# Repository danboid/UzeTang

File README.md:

# UzeTang

A [Uzebox](https://uzebox.org) console core for the **Sipeed Tang Nano 20K**
FPGA, based on the [Uzebox Omega](https://github.com/danboid/uzebox-omega) design.

- **CPU:** a new, cycle-exact ATmega644 core. It is verified in lock-step,
  cycle by cycle, against the
  [CUzeBox-ex](https://github.com/weber21w/cuzebox-ex) emulator.
- **Video and audio:** HDMI at 720×480p, 59.94 Hz, with 48 kHz audio. There is
  no composite output and no AD725.
- **Games:** loaded from the micro SD card by the standard Uzebox
  **Bootloader5** game loader, which ships in the bitstream.
- **Controllers:** two SNES pads on the same pins and adapters as
  [SNESTang](https://github.com/nand2mario/snestang/blob/main/doc/installation.md).
- **SPI RAM:** 8 MB, emulated in the board's built-in SDRAM (all of it)
  (23LC1024-compatible: READ, WRITE, RDMR and WRMR, with byte, page and
  sequential modes; 24-bit addresses). The kernel's `SpiRamInitGetSize()`
  reports 128 banks of 64 KB, as CUzeBox-ex does with 8 MB.

Not implemented yet: DualShock 2 adapters (their pins are kept free) and EEPROM saving
across power cycles. There are likely other missing features.

There is an experimental UzeTang PCB that fits within the Uzebox 3D printed case but
it has not been tested at all yet so try it at your own risk.

I don't plan to port it to any other Tang boards but I would like to see it ported
to the Spectrum Next, MEGA65 and other open source modern retro FPGA based computers.

See [this forum topic](https://uzebox.org/forums/viewtopic.php?t=11951) for discussion and more information about UzeTang.

## Hardware

| Function | Tang Nano 20K pins | Notes |
|---|---|---|
| HDMI | on-board connector | 720×480p, 4:3, HDMI with 48 kHz audio |
| micro SD | on-board slot | SPI mode, FAT16/FAT32, SD and SDHC |
| SNES pad 1 | latch 28, clock 27, data 25 | as SNESTang |
| SNES pad 2 | latch 29, clock 26, data 30 | as SNESTang |
| S1 button | 88 | reset (see below) |
| S2 button | 87 | hold for free-running video (no frame lock), for diagnosis |
| LED0 / LED1 | 15 / 16 | SD access / slow blink = video OK, fast blink = no video sync |

Pins 17–20 (SNESTang's DualShock 2 adapter) are left unused.

## Using it

1. Format a micro SD card as FAT32 (or FAT16) and copy `.uze` games onto it.
2. Flash the bitstream to the Tang Nano 20K (see [Flashing](#flashing)).
3. Power up. As on a real Uzebox, Bootloader5 first watches the controller for
   about ¾ s:
   - If the card holds exactly one `.uze`, it is flashed and started.
   - Otherwise the **game selector** opens.
   - At power-up the AVR's flash and EEPROM are blank, so you always start in
     the selector.
4. Choose a game with **Up/Down** and press **Start** (or Select). The game is
   written into the AVR's flash, which takes a second or two, and then starts.
5. **S1** resets the console. Hold any pad button while pressing S1 to return to
   the selector. **B** in the selector switches between "reset starts the game"
   and "reset opens the menu"; this setting is kept until power-off. In game,
   Start+Select+Y+B is the usual Uzebox soft reset.

## Flashing

UzeTang is flashed like any other Tang Nano 20K core, with openFPGALoader or
the Gowin programmer.

### Installing openFPGALoader on Debian and Ubuntu

openFPGALoader is in the standard Debian and Ubuntu repositories:

```
sudo apt update
sudo apt install openfpgaloader
```

Older releases ship an old version that does not know the Tang Nano 20K
(`openFPGALoader --list-boards | grep tangnano20k` prints nothing). In that
case build it from source, as described in the
[openFPGALoader install guide](https://trabucayre.github.io/openFPGALoader/guide/install.html)
and Sipeed's [Flashing on Linux](https://wiki.sipeed.com/hardware/en/tang/Tang-Nano-Doc/flash-in-linux.html)
page:

```
sudo apt install git gzip libftdi1-2 libftdi1-dev libhidapi-hidraw0 libhidapi-dev \
    libudev-dev zlib1g-dev cmake pkg-config make g++
git clone https://github.com/trabucayre/openFPGALoader.git
cd openFPGALoader && mkdir build && cd build
cmake .. && make -j$(nproc) && sudo make install
```

To use it without `sudo`, install the udev rules (see the install guide) and
add yourself to the `plugdev` group.

### Writing the bitstream

Connect the Tang Nano 20K by USB, then:

```
openFPGALoader -f uzetang.fs
```

`-f` writes to the board's flash, so UzeTang starts every time the board is
powered on. Add `-b tangnano20k` if openFPGALoader does not detect the board
on its own. Without `-f`, the bitstream is only loaded into the FPGA and is
lost at power-off, which is handy for a quick test.

Alternatively you can try flashing uzetang-oss.fs which is the same code
synthesized into a bitstream using an open source toolchain.

## Building

### Installing the Gowin IDE

Follow Sipeed's [Install the IDE](https://wiki.sipeed.com/hardware/en/tang/Tang-Nano-Doc/install-the-ide.html)
guide. In short:

- Download the **Education Edition** from Gowin's website. It needs no licence;
  the Standard Edition needs a licence file from Gowin.
- On Linux, unpack the archive. The tools are in its `IDE/bin` folder (`gw_ide`
  for the IDE, `gw_sh` for scripted builds such as UzeTang's).
- On Windows, run the installer with all components selected, then install the
  two drivers it offers.
- Sipeed suggests openFPGALoader (above) for flashing on Linux, as the Gowin
  programmer does not always work with the Tang boards' USB-JTAG.

### Gowin EDA

From the UzeTang folder (adjust the path to where you unpacked Gowin):

```
env -u DISPLAY -u WAYLAND_DISPLAY QT_QPA_PLATFORM=offscreen LIBGL_ALWAYS_SOFTWARE=1 \
    ~/Gowin_V1.9.11.03_Education_Linux/IDE/bin/gw_sh build.tcl
```

This produces `impl/pnr/uzetang.fs`. Use the Gowin Education Edition 1.9.9 or
newer, the same as SNESTang (tested with V1.9.11.03 on Debian 12). This build
uses Gowin's own I/O settings for the pad pins (pull-ups) and emulated LVDS
for HDMI, exactly as SNESTang does.

`gw_sh` has no window, but it still loads Qt and OpenGL. The `env` settings
above hide the desktop from it and ask for software rendering. Without them,
`gw_sh` can abort with "Could not load the Qt platform plugin "xcb"" and a
core dump, or with `libGL error` / `X Error ... GLX`. If it still fails,
install Mesa's OpenGL drivers (`sudo apt install libgl1-mesa-dri`), or run it
in a virtual X server (`sudo apt install xvfb`, then
`xvfb-run -a .../gw_sh build.tcl`).

The timing report (`impl/pnr/uzetang.tr.html`) lists setup and hold
violations for a clock called `sys/hdmi_out/aud_acc[0]`. They are false: that
is the 48 kHz audio clock, which is made from the pixel clock and only feeds
the HDMI audio sample handover. Gowin assumes it runs at 100 MHz with no
relationship to the pixel clock. Check `clk_cpu` (28.688 MHz needed) and
`clk_pix` (27 MHz needed) in the Max Frequency Summary instead.

### Open source (yosys + nextpnr-himbaechel + apicula)

```
NEXTPNR=nextpnr-himbaechel syn/oss_build.sh
```

This produces `syn/out/uzetang_oss.fs`. yosys cannot read hdl-util's
SystemVerilog HDMI encoder, so this flow uses `rtl/hdmi/hdmi_lite.v`, a plain
Verilog HDMI encoder written for UzeTang. It sends real HDMI with:

- data islands on every line (two packets each);
- an AVI InfoFrame (RGB, 4:3, full range, IT content / graphics);
- an Audio InfoFrame, Audio Clock Regeneration (N 6144, CTS 27000) and 48 kHz
  L-PCM audio sample packets;
- vsync edges aligned with the hsync leading edge, as CEA-861 requires, and at
  least 12 control characters before every preamble, as the HDMI compliance
  test requires.

apicula only allows true LVDS buffers on the HDMI pins, so this flow uses
`TLVDS_OBUF`. The Gowin flow uses emulated LVDS (`ELVDS_OBUF`), as SNESTang
does.

**SNES pads and I/O bank 5.** The SNES pad pins (25–30) share I/O bank 5 with
the HDMI pins. With true LVDS outputs in the bank, apicula's `gowin_pack`
(0.35) configures the whole bank for a low voltage, and it also sets two
configuration bits on the pad data inputs differently from the Gowin IDE: it
leaves `CLAMP=PCI` off and sets an input-standard bit that belongs to the
differential / reference-voltage standards. With that bitstream the pad data
line reads wrongly. Every pressed button also shows up as the next one in the
SNES bit order, B reads as held, and START reads as START+UP, so Bootloader5
loads the game above the highlighted one.

`syn/oss_build.sh` therefore packs through `tools/gowin_pack_bank33.py`, a
small wrapper around apicula's `gowin_pack`. It keeps banks with LVDS outputs
at the board's real 3.3 V and sets those pad-input bits as the Gowin IDE sets
them. The pad pins' I/O configuration then decodes identically to the Gowin
build's, and the pads work in both builds. To check that against a Gowin
bitstream, `tools/gowin_pack_bank33.py --iob-from uzetang.fs ...` copies the
pad tiles' I/O fuses from it instead.

The results below are from yosys 0.33 and nextpnr-himbaechel master
(Nov 2026), for the GW2AR-LV18QN88C8/I7:

| Resource | Used | Available |
|---|---|---|
| LUT4 (after packing, nextpnr) | 15,610 | 20,736 (75%) |
| Flip-flops | 2,544 | 15,552 (16%) |
| Block RAM | 41 | 46 (89%) |
| AVR clock Fmax | 31.7 MHz | needs 28.69 MHz |
| Pixel clock Fmax | 66 MHz | needs 27 MHz |

### Bootloader

The AVR flash's boot section (0xF000) holds Bootloader5 as the block RAM's
initial contents, generated from `firmware/bootloader5.hex`:

```
python3 tools/hex2mem.py --gowin-init firmware/bootloader5.hex rtl/bootloader_init.vh
```

## Verification

All test benches are in `sim/` (Verilator):

- **`tb_lockstep`** (`Vavr_soc`, or `Vls_top` with the SPI RAM emulation, the
  SDRAM controller and an SDRAM model) compiles the CUzeBox-ex AVR core in as a
  reference.
  - At every instruction it compares PC, cycle count, r0–r31, SREG and SP.
  - Every *N* instructions it also compares all of SRAM and the I/O registers.
  - `tests/run_fuzz.sh` generates random instruction streams, with Timer1,
    SPI and USART interrupts, PINx toggles, 16-bit timer writes and EEPROM
    strobes.
  - `tests/run_demos.sh` runs the Uzebox repository's games and demos, which
    are built with `tools/build_demo.py`.
- **`sim/hdmi`** checks the open-source HDMI encoder. `tb_hdmi.v` (Icarus
  Verilog) writes three frames of TMDS symbols, and `check_hdmi.py` decodes
  them the way a display does. It checks the period structure and guard
  bands, every video pixel, sync timing, the BCH ECC of every packet,
  InfoFrame checksums, ACR values, and the audio samples (values, order,
  parity, channel status). The checker also decodes hdl-util's output with
  no packet errors (`sim/hdmi/ref`).
- **`tests/demos_src/SpiRam8M`** detects the SPI RAM size and writes and reads
  patterns in all 128 banks, including blocks that cross bank boundaries. It
  passes in lock-step with CUzeBox-ex set to 8 MB (`Vls_top` built with
  `-DLS_SPIRAM_BITS=23`, run with `-r 128`).
- **`tb_system`** (`Vsim_system`, or `Vsim_system` in `sysobj_lite` with the
  open-source HDMI encoder) simulates the whole board design with real
  clock ratios: frame lock, HDMI encoder input, SDRAM, a bit-level SD card
  model with CRC serving a FAT32 image, scripted pad presses, and SNES mouse
  moves and clicks (`-m`). It writes the HDMI frames as images and can record
  the audio output as a WAV file (`-a`). It covers the whole path: power-up,
  Bootloader5's menu, flashing a game from SD, booting it, and pad detection
  and buttons.

**Known deliberate difference from CUzeBox-ex:** PINA returns the *live* pad
data lines, as a real AVR does. The emulator latches them on PORTA writes. This
only shows if PINA is read before PORTA is first written, or if a program
clocks a missing pad more than 32 times.

## Licence

GPL v3 or later. `rtl/hdmi/` contains hdl-util/hdmi (MIT OR Apache-2.0),
used by the Gowin flow; `rtl/hdmi/hdmi_lite.v` is UzeTang's own (GPL v3). The
test benches include CUzeBox and CUzeBox-ex sources (GPL v3). Bootloader5 and
the Uzebox kernel are from the Uzebox project (GPL v3).

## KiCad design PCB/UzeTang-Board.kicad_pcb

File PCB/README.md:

# UzeTang Board v1.0

A carrier PCB that turns a Sipeed **Tang Nano 20K** into a boxed console for
[UzeTang](https://github.com/danboid/UzeTang) and SNESTang, in the
[Uzebox 3D-printed case](https://github.com/Uzebox/uzebox/tree/master/cad/Enclosures/Uzebox/V2.0).

- **Same outline and holes as the Uzebox V5.0 / Omega board:** 100 × 81 mm,
  M3 holes at (3, 3), (97, 3) and (55.14, 71.15), the two light-pipe holes and
  the four rubber-foot positions. The corners are rounded to a 3 mm radius,
  centred on the front mounting holes.
- **Same front panel:** both SNES sockets, the RESET and USER buttons and the
  power LED sit exactly where the Uzebox has them, so the case's button caps
  and light pipe line up.
- **Same SD socket in the same place** (Würth 693063020911 at (83.82, 52.07),
  card in from the back), wired with all six SD lines so SNESTang can use 4-bit
  SD mode as well as UzeTang's SPI mode.
- **Tang Nano 20K on two 1×20 female headers**, rotated so that its **HDMI
  socket faces the back of the case** (it overhangs the rear edge by about
  2 mm). Its USB-C faces the front, inside the case: use a short USB-C
  extension with a panel-mount end in the rear wall for power and flashing.
- **Removable ESP-12F** (Uzenet) on two 8-pin 2 mm receptacles, as on the
  Uzebox, with its own LD1117V33 regulator fed from the Tang's 5 V. The whole
  ESP section is optional.
- **Optional analog audio** on two RCA jacks, the same white and red jacks
  the Uzebox uses, each fed by a 1-bit DAC from the FPGA through a resistor
  and two capacitors. HDMI audio is unaffected. The whole audio section is
  optional.
- **Optional EXT expansion header** (J6, 2×10, 2.54 mm) with every Tang I/O
  pin the board doesn't use, plus 3.3 V, 5 V and GND.
- Everything is through-hole except the SD socket (the same SMD socket the
  Uzebox uses). Two-layer board, GND poured on both sides.

Coordinates in this file are Uzebox V5.0 board coordinates: mm from the
front-left corner, y towards the back.

## Files

| File | What it is |
|---|---|
| `UzeTang-Board.kicad_pro` / `.kicad_pcb` / `.kicad_sch` | KiCad 7 project (opens in KiCad 7 and later) |
| `UzeTang-Board.pretty/`, `UzeTang-Board.kicad_sym` | Project footprint and symbol libraries (referenced by `fp-lib-table` / `sym-lib-table`) |
| `UzeTang-Board.kicad_dru` | Custom design rules (see *DRC* below) |
| `bom/UzeTang-Board-BOM-DigiKey.xlsx` | Digi-Key BOM; set the number of boards in F3 |
| `gerbers/` | Gerbers and drill file, ready to upload to a PCB fab |
| `docs/` | Renders of the copper layers, silkscreen and schematic |
| `gen/` | Scripts that generate everything (see *Regenerating*) |

## Pin assignments

| Function | Tang Nano 20K pin | Notes |
|---|---|---|
| SNES P1 latch / clock / data | 28 / 27 / 25 | Same as SNESTang and UzeTang; 4.7k pull-up on data |
| SNES P2 latch / clock / data | 29 / 26 / 30 | Same as SNESTang and UzeTang; 4.7k pull-up on data |
| SD CLK / CMD / DAT0 / DAT1 / DAT2 / DAT3 | 73 / 74 / 75 / 77 / 86 / 76 | 10k pull-ups on DAT0-DAT3 |
| RESET button | 71 | Active high, 10k pull-down (like the Tang's S1) |
| USER button | 72 | Active high, 10k pull-down (like the Tang's S2) |
| ESP-12F RXD (FPGA TX) / TXD (FPGA RX) | 48 / 49 | |
| ESP-12F RST | 31 | Also pulled up to the ESP's 3.3 V |
| Power LED | - | From the Tang's 3.3 V through 330 Ω |
| Audio left / right (1-bit DAC) | 52 / 53 | Through the filters to J4 / J5 (optional) |
| EXT header (J6) | 15-20, 41, 42, 51, 54, 55, 56, 79, 80, 85 | Every other Tang I/O; see below |

SNES pads and the SD card run from the Tang's 3.3 V pins.

## Firmware changes

The SNES pads need no changes. The buttons and SD card use different pins from
the bare Tang Nano 20K, so the bitstreams need a board constraint file:

- **UzeTang:** `rtl/tang20k/uzetang_board.cst` holds the board's pins. Build
  with `CST=uzetang_board.cst syn/oss_build.sh` (open-source tools) or
  `UZETANG_CST=uzetang_board.cst gw_sh build.tcl` (Gowin). The default build
  still targets a bare Tang Nano 20K.
- **SNESTang:** in `nano20k.cst`, move the two buttons to 71 / 72 and the SD
  lines to the pins in the table above. Both stay active high, as on the
  Tang's own buttons.

## Analog audio (optional)

Two RCA jacks at the back carry line-level audio, alongside HDMI audio:

- **J4, white, left** sits exactly where the Uzebox has its AUDIO jack.
- **J5, red, right** sits where the Uzebox has its DC power jack. Seen from
  behind the console, white is on the left and red on the right.

Each channel is one FPGA pin driving a 1-bit sigma-delta DAC, then a 1k / 10 nF
low pass (corner about 16 kHz) and a 10 µF DC-blocking capacitor: three parts
per channel. The output is up to 3.3 V peak to peak, centred on 0 V after the
capacitor; that is a normal line level for a TV or amplifier input.

UzeTang drives both pins with the same mono Uzebox sound (it is a mono
console), the same signal it sends over HDMI. Stereo needs a core that
produces stereo, such as SNESTang if analog output were added to it: it would
use pins 52 and 53 the same way.

HDMI audio is unaffected: the DAC uses two spare header pins, and the FPGA
generates both outputs from the same samples.

Leave out J4, J5, R14, R15 and C10-C13 for a board without analog audio.

## EXT expansion header (optional)

J6 is a 2×10, 2.54 mm pin header at the front right, between the Tang and the
USER button, so a ribbon cable or a small add-on board can reach every FPGA
pin the board doesn't use. It is clear of the Tang's USB-C plug. Pin 1 (square
pad) is at the front left; odd pins are in the front row.

| J6 pin | Signal | J6 pin | Signal |
|---|---|---|---|
| 1 | 3.3 V | 2 | 5 V |
| 3 | Tang pin 15 | 4 | Tang pin 16 |
| 5 | Tang pin 17 | 6 | Tang pin 18 |
| 7 | Tang pin 19 | 8 | Tang pin 20 |
| 9 | Tang pin 41 | 10 | Tang pin 42 |
| 11 | Tang pin 51 | 12 | Tang pin 54 |
| 13 | Tang pin 55 | 14 | Tang pin 56 |
| 15 | Tang pin 79 | 16 | Tang pin 80 |
| 17 | Tang pin 85 | 18 | GND |
| 19 | GND | 20 | GND |

All signals are 3.3 V LVCMOS straight from the FPGA, with nothing in between:
don't connect 5 V logic to them. Some of them also go to parts on the Tang
Nano 20K itself, so check its schematic before using them:

- 15-20 drive the Tang's six onboard LEDs (lit when the pin is low).
- 79 drives the Tang's WS2812 RGB LED.
- 80 and 85 are shared with the Tang's own micro SD slot: leave that slot
  empty if you use them.

The 3.3 V and 5 V pins come from the Tang's supply (5 V is the USB-C supply),
so keep the load small.

If the ESP-12F or the analog audio parts aren't fitted, their pins (31, 48 and
49; 52 and 53) are free too, but they don't go to J6.

## Updating the ESP-12F firmware

The ESP-12F's serial port is wired only to the FPGA (pins 48 and 49), and its
GPIO0 is pulled high by R12, so on this board it always starts its normal
firmware. To flash new firmware, unplug the ESP-12F from its sockets and use
an ESP-12 programming adapter.

## Building one

1. Order the PCB from the files in `gerbers/` (2 layers, 1.6 mm, any colour).
2. Solder the SD socket first (it is the only SMD part), then the low parts:
   resistors, ceramic capacitors, LED, buttons, then the taller parts.
3. Fit the two 1×20 female headers for the Tang Nano 20K. Plug the Tang in
   while soldering them so they stay straight. Mind the orientation: the
   silkscreen shows where the HDMI and USB-C ends go, and the HDMI end goes to
   the back edge.
4. The SNES sockets solder to pads on the front edge, as on the Uzebox.
5. ESP-12F (optional): solder the 2 mm male headers to the module, and the two
   2 mm receptacles, C6-C9 and R10-R13 to the board.
6. The LD1117V33 (U3) lies flat, tab down, with its body towards the back of
   the board: bend its legs down 90° so the hole in the tab lines up with the
   hole in the board, then solder it. An M3 screw and nut through the tab is
   optional. There is no top-side copper under the tab, which is connected to
   the 3.3 V output.
7. Analog audio (optional): R14, R15, C10-C13 and the two RCA jacks. The
   jacks' plastic pegs locate them; the barrels point out of the back edge.
8. EXT header (optional): J6, long pins up, square pad (pin 1) at the front
   left.

### Fitting the case

The case's back wall was built for the Uzebox's DC jack, mini-DIN and RCA
jacks. Cut or redesign the rear openings for:

- the Tang Nano 20K's **HDMI socket**, centred about 30 mm from the board's
  left edge. Its height depends on the headers: with standard 8.5 mm female
  headers the Tang's PCB sits about 11 mm above this board, and the HDMI
  socket is on top of it. Measure your assembled board before modelling the
  opening.
- a panel-mount **USB-C** extension (the Tang's USB-C faces the front inside
  the case).

If you fit the optional audio jacks, they reuse two of the Uzebox positions:

- the **left jack** (J4, white) is where the Uzebox has its AUDIO jack, so the
  existing opening fits. It is 0.2 mm to the right of the Uzebox position, to
  keep its locating peg clear of the Tang module's edge.
- the **right jack** (J5, red) is centred on the Uzebox DC jack's position
  (x = 7.62 mm). The DC jack's opening is a different shape, so it may need
  opening out to fit an RCA barrel.

The SD card slot and all the front-panel openings stay as they are. There is
about 22 mm of headroom above the PCB, enough for the Tang on 8.5 mm headers.

## DRC

Run DRC in KiCad's PCB editor. Expected results:

- No violations at all in KiCad 10.
- The SNES socket pads reach the front edge, exactly as on the Uzebox board.
  A rule in `UzeTang-Board.kicad_dru` sets the edge-clearance check to
  *ignore* for J1 and J2, which KiCad 10 honours. The KiCad 7 Python DRC in
  `gen/drc.py` still lists those 14 pads.

## Regenerating

The board, schematic and BOM are generated from `gen/design.py`, which holds
the part list, positions and nets. You can edit the KiCad files by hand, or
change `design.py` and regenerate:

```sh
# KiCad 7 (pcbnew Python module), Java 17+, Freerouting 1.9 and xvfb-run
python3 gen/make_footprints.py <uzebox-omega>/.../Uzebox_Omega.pretty UzeTang-Board.pretty  # only if footprints change
FREEROUTING=/path/to/freerouting.jar gen/route.sh   # place, autoroute, pour GND, DRC, schematic
python3 gen/check_netlist.py                       # schematic netlist == board netlist
python3 gen/make_bom.py                             # Digi-Key BOM
```

`route.sh` retries the autorouter until DRC reports no unconnected items.
`design.PREROUTES` holds one hand-placed +3V3 track that Freerouting keeps.

## Licence

CERN-OHL-S-2.0. The SNES, tactile switch, SD socket and LED footprints come
from the Uzebox Omega v1.5 KiCad project; the Tang Nano 20K pinout comes from
the MiSTeryShield20k project.

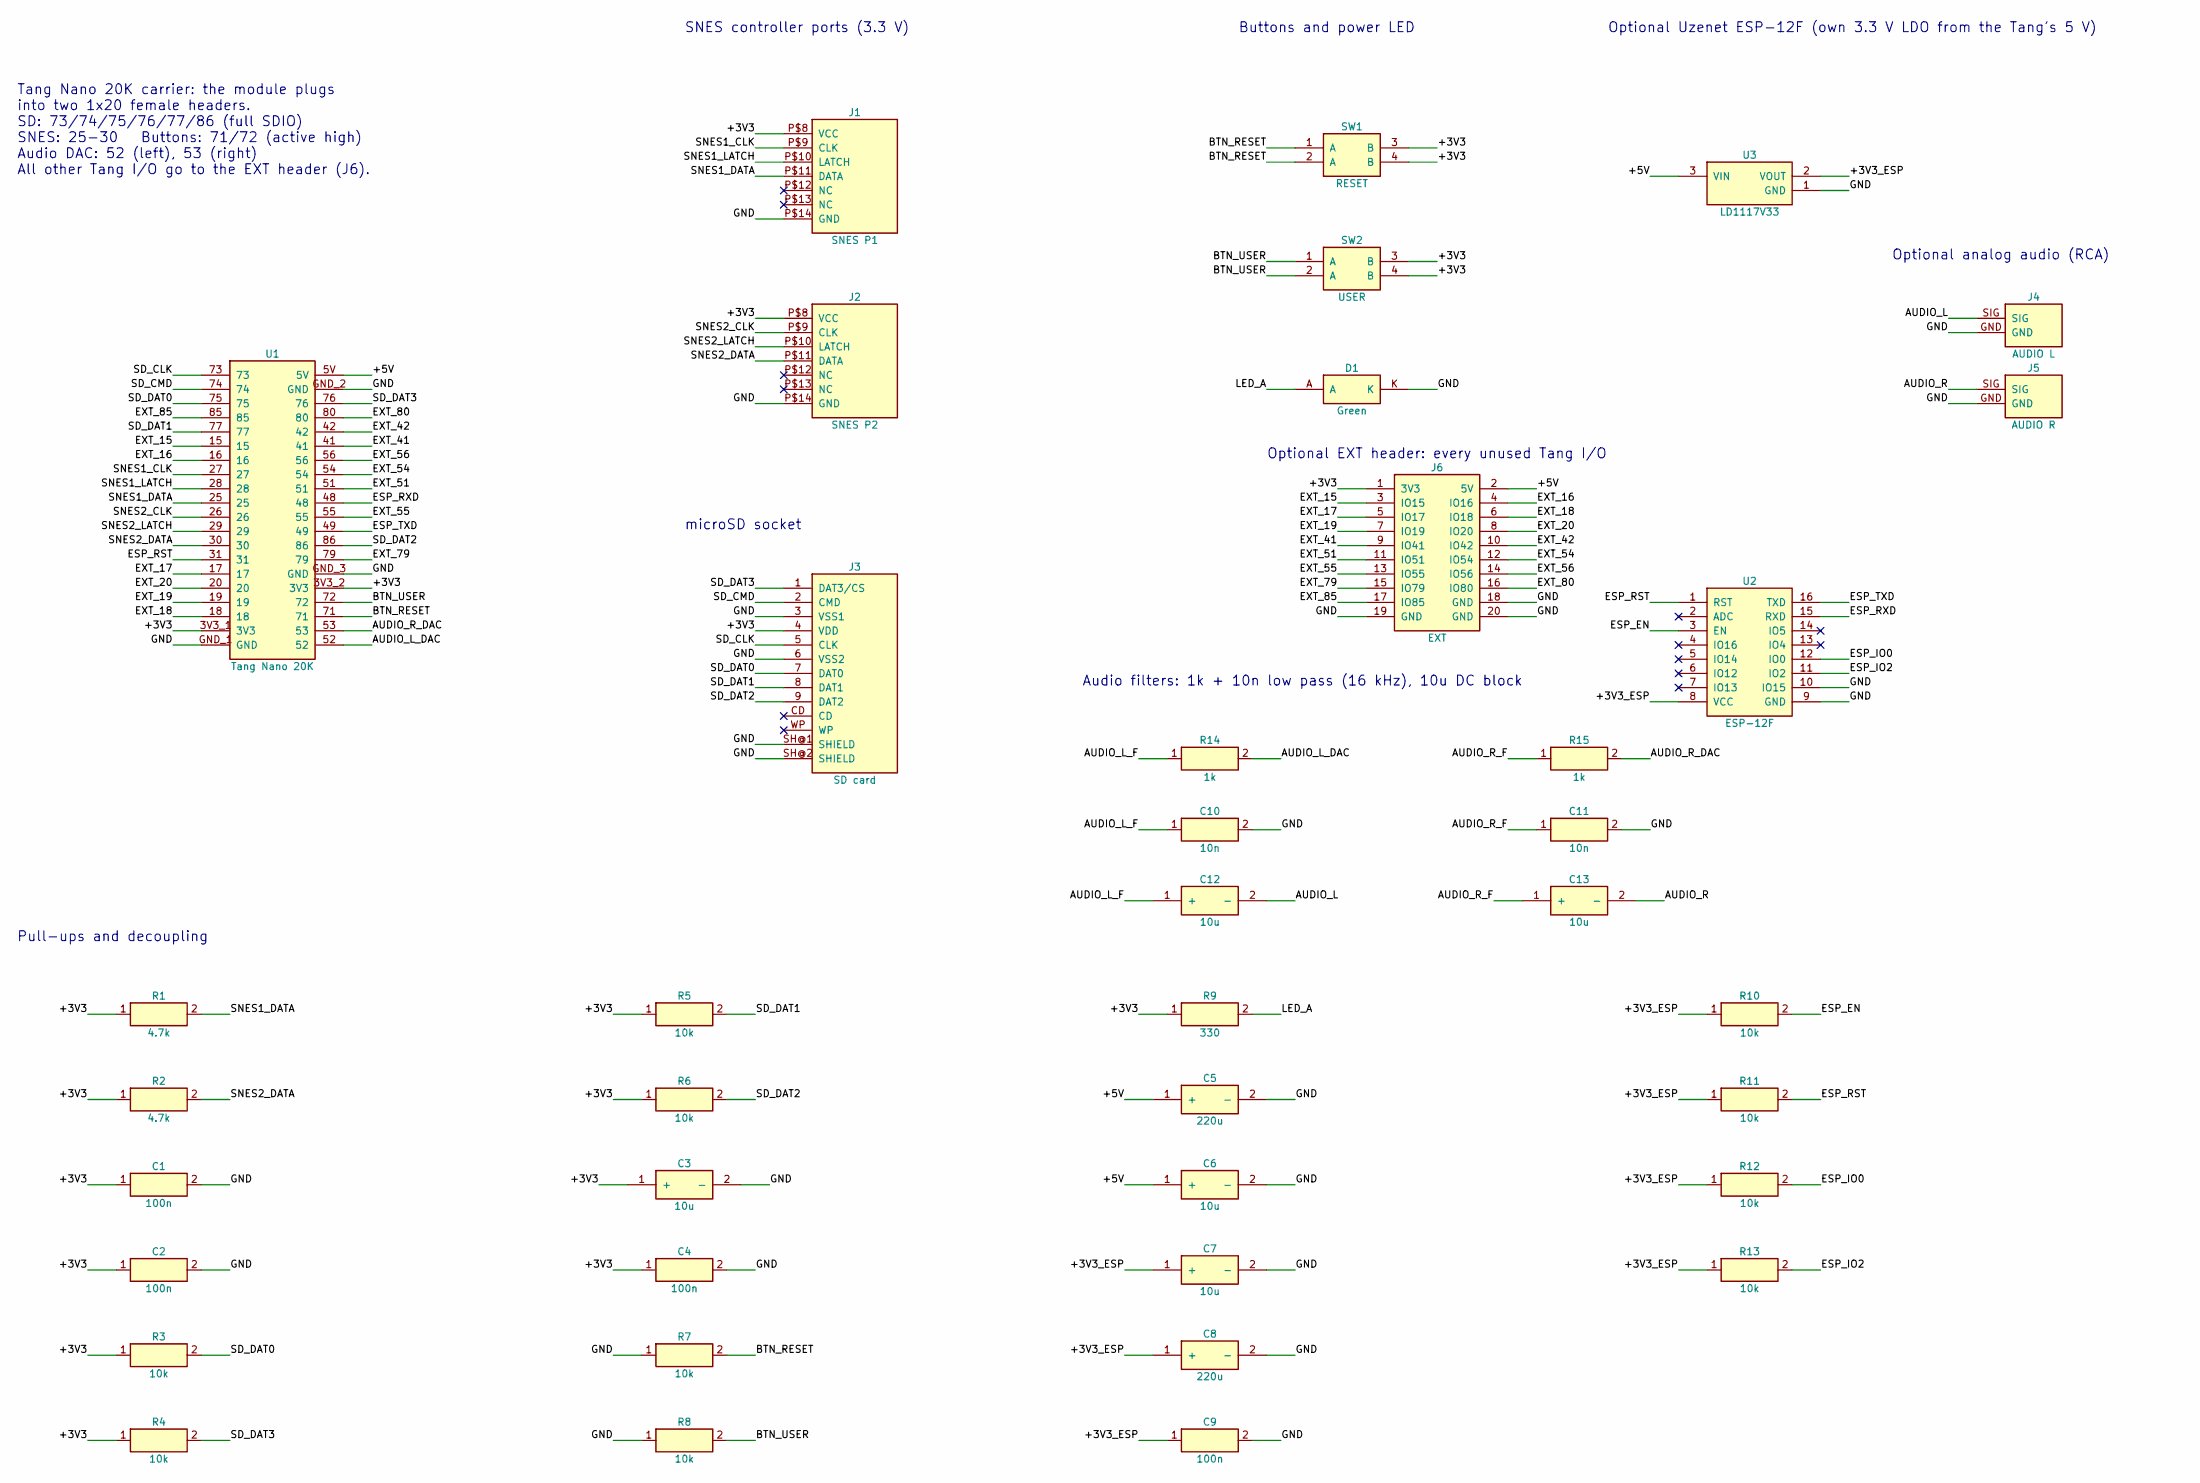
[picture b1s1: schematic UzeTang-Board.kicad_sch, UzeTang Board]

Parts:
C1, C2, C4, C9: 100n; C_Disc_D3.8mm_W2.6mm_P2.50mm
C3, C6, C7, C12, C13: 10u; CP_Radial_D5.0mm_P2.00mm
C5, C8: 220u; CP_Radial_D6.3mm_P2.50mm
C10, C11: 10n; C_Disc_D3.8mm_W2.6mm_P2.50mm
D1: Green; LED3MM
J1: SNES P1; SNES_CONNECTOR
J2: SNES P2; SNES_CONNECTOR
J3: SD card; SDCARD_4UCONN
J4: AUDIO L; RCA
J5: AUDIO R; RCA
J6: EXT; PinHeader_2x10_P2.54mm_Vertical
R1, R2: 4.7k; R_Axial_DIN0207_L6.3mm_D2.5mm_P10.16mm_Horizontal
R3, R4, R5, R6, R7, R8, R10, R11, R12, R13: 10k; R_Axial_DIN0207_L6.3mm_D2.5mm_P10.16mm_Horizontal
R9: 330; R_Axial_DIN0207_L6.3mm_D2.5mm_P10.16mm_Horizontal
R14, R15: 1k; R_Axial_DIN0207_L6.3mm_D2.5mm_P10.16mm_Horizontal
SW1: RESET; TACTILE-PTH
SW2: USER; TACTILE-PTH
U1: Tang Nano 20K; TangNano20K
U2: ESP-12F; ESP-12F_Socket_2mm
U3: LD1117V33; TO-220-3_Horizontal_TabDown

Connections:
+3V3: C1.1, C2.1, C3.1 (+), C4.1, J1.P$8 (VCC), J2.P$8 (VCC), J3.4 (VDD), J6.1 (3V3), R1.1, R2.1, R3.1, R4.1, R5.1, R6.1, R9.1, SW1.3 (B), SW1.4 (B), SW2.3 (B), SW2.4 (B), U1.3V3_1 (3V3), U1.3V3_2 (3V3)
+3V3_ESP: C7.1 (+), C8.1 (+), C9.1, R10.1, R11.1, R12.1, R13.1, U2.8 (VCC), U3.2 (VOUT)
+5V: C5.1 (+), C6.1 (+), J6.2 (5V), U1.5V, U3.3 (VIN)
AUDIO_L: C12.2 (-), J4.SIG
AUDIO_L_DAC: R14.2, U1.52
AUDIO_L_F: C10.1, C12.1 (+), R14.1
AUDIO_R: C13.2 (-), J5.SIG
AUDIO_R_DAC: R15.2, U1.53
AUDIO_R_F: C11.1, C13.1 (+), R15.1
BTN_RESET: R7.2, SW1.1 (A), SW1.2 (A), U1.71
BTN_USER: R8.2, SW2.1 (A), SW2.2 (A), U1.72
ESP_EN: R10.2, U2.3 (EN)
ESP_IO0: R12.2, U2.12 (IO0)
ESP_IO2: R13.2, U2.11 (IO2)
ESP_RST: R11.2, U1.31, U2.1 (RST)
ESP_RXD: U1.48, U2.15 (RXD)
ESP_TXD: U1.49, U2.16 (TXD)
EXT_15: J6.3 (IO15), U1.15
EXT_16: J6.4 (IO16), U1.16
EXT_17: J6.5 (IO17), U1.17
EXT_18: J6.6 (IO18), U1.18
EXT_19: J6.7 (IO19), U1.19
EXT_20: J6.8 (IO20), U1.20
EXT_41: J6.9 (IO41), U1.41
EXT_42: J6.10 (IO42), U1.42
EXT_51: J6.11 (IO51), U1.51
EXT_54: J6.12 (IO54), U1.54
EXT_55: J6.13 (IO55), U1.55
EXT_56: J6.14 (IO56), U1.56
EXT_79: J6.15 (IO79), U1.79
EXT_80: J6.16 (IO80), U1.80
EXT_85: J6.17 (IO85), U1.85
GND: C1.2, C2.2, C3.2 (-), C4.2, C5.2 (-), C6.2 (-), C7.2 (-), C8.2 (-), C9.2, C10.2, C11.2, D1.K, J1.P$14 (GND), J2.P$14 (GND), J3.3 (VSS1), J3.6 (VSS2), J3.SH@1 (SHIELD), J3.SH@2 (SHIELD), J4.GND, J5.GND, J6.18 (GND), J6.19 (GND), J6.20 (GND), R7.1, R8.1, U1.GND_1 (GND), U1.GND_2 (GND), U1.GND_3 (GND), U2.9 (GND), U2.10 (IO15), U3.1 (GND)
LED_A: D1.A, R9.2
SD_CLK: J3.5 (CLK), U1.73
SD_CMD: J3.2 (CMD), U1.74
SD_DAT0: J3.7 (DAT0), R3.2, U1.75
SD_DAT1: J3.8 (DAT1), R5.2, U1.77
SD_DAT2: J3.9 (DAT2), R6.2, U1.86
SD_DAT3: J3.1 (DAT3/CS), R4.2, U1.76
SNES1_CLK: J1.P$9 (CLK), U1.27
SNES1_DATA: J1.P$11 (DATA), R1.2, U1.25
SNES1_LATCH: J1.P$10 (LATCH), U1.28
SNES2_CLK: J2.P$9 (CLK), U1.26
SNES2_DATA: J2.P$11 (DATA), R2.2, U1.30
SNES2_LATCH: J2.P$10 (LATCH), U1.29

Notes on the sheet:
Tang Nano 20K carrier: the module plugs into two 1x20 female headers. SD: 73/74/75/76/77/86 (full SDIO) SNES: 25-30 Buttons: 71/72 (active high) Audio DAC: 52 (left), 53 (right) All other Tang I/O go to the EXT header (J6).
SNES controller ports (3.3 V)
Buttons and power LED
microSD socket
Optional Uzenet ESP-12F (own 3.3 V LDO from the Tang's 5 V)
Pull-ups and decoupling
Audio filters: 1k + 10n low pass (16 kHz), 10u DC block
Optional analog audio (RCA)
Optional EXT header: every unused Tang I/O

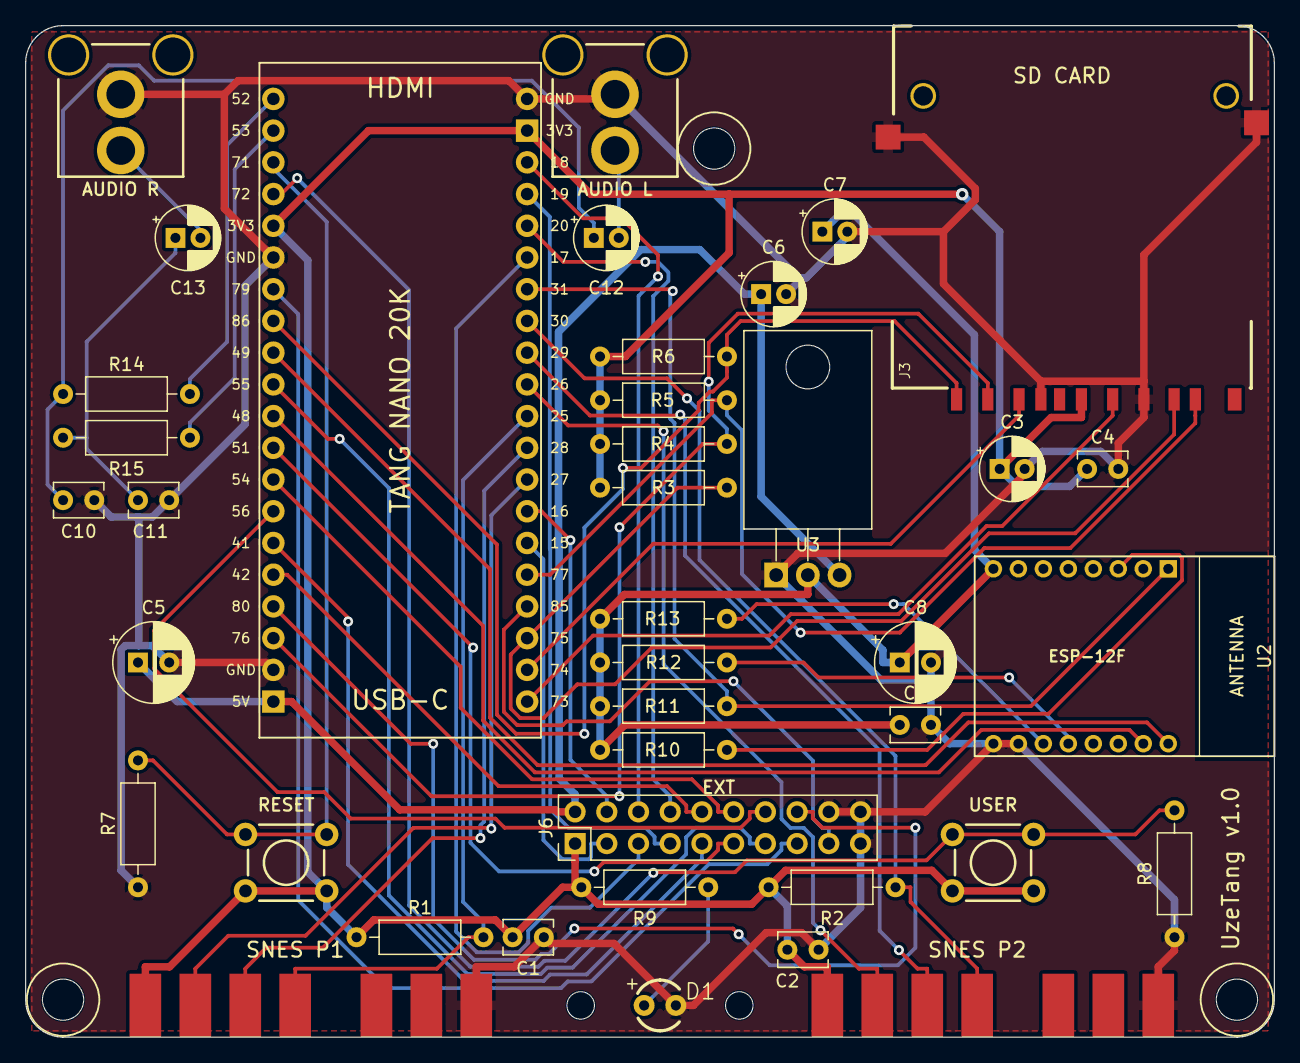
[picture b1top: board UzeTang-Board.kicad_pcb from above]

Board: 2 copper layers, 100.0 x 81.0 mm, 49 parts (0 on the bottom side), 46 nets.

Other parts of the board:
BUMP1, BUMP2, BUMP3, BUMP4: Bumpon
H1, H2, H3: MountingHole_3.3mm_Uzebox
H4, H5: Hole_2.2mm_LightPipe
